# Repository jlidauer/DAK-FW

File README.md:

# DAK
### Double Action Keyboard Firmware
This firmware is used for Double Action Keyboards with Teensy microcontrollers. Currently the firmware provides two independed layers _(normal-layer and FN-layer)_, both of these layers support double action _(first action, second action)_. This means that each double action key can be configured to have up to four independent actions. The firmware is developed using the Arduino IDE with the Teensyduino add-on.

### Double Action Keyboard PCB V1.0
An example implementation a double action keyboard PCB can be found in the PCB directory.

### What is a Double Action Keyboard?
A double action keyboard has switches that have two physical positions (two steps). Each key has two different functions that can be triggered without pressing modifier keys, this makes typing of special characters easier. For example, when pressing a key one step down, the keyboard could send a normal key stroke (e.g., `KEY_A`), and if the same key would be pressed two steps down instead, the keyboard could send the key combination of a special character (e.g., `ALTGR + KEY_9`). 

More info can be found in the Wiki: [Building a Double Action Keyboard](https://github.com/jlidauer/DAK/wiki/Building-a-Double-Action-Keyboard).

### Compatible microcontrollers:
In principle all Teensy microcontrollers with keyboard funtionality should work.

The firmware has been tested with the following microcontrollers:
- Teensy 3.2
- Teensy-LC

### How to use this firmware?
See the Wiki for instructions: [Getting Started](https://github.com/jlidauer/DAK/wiki/Getting-Started)

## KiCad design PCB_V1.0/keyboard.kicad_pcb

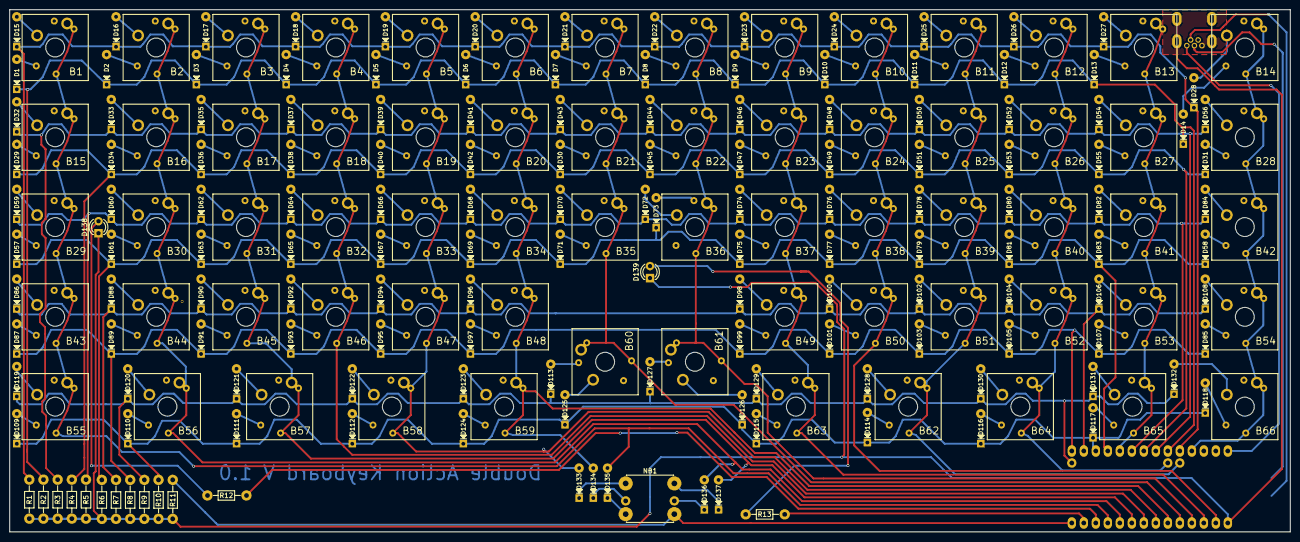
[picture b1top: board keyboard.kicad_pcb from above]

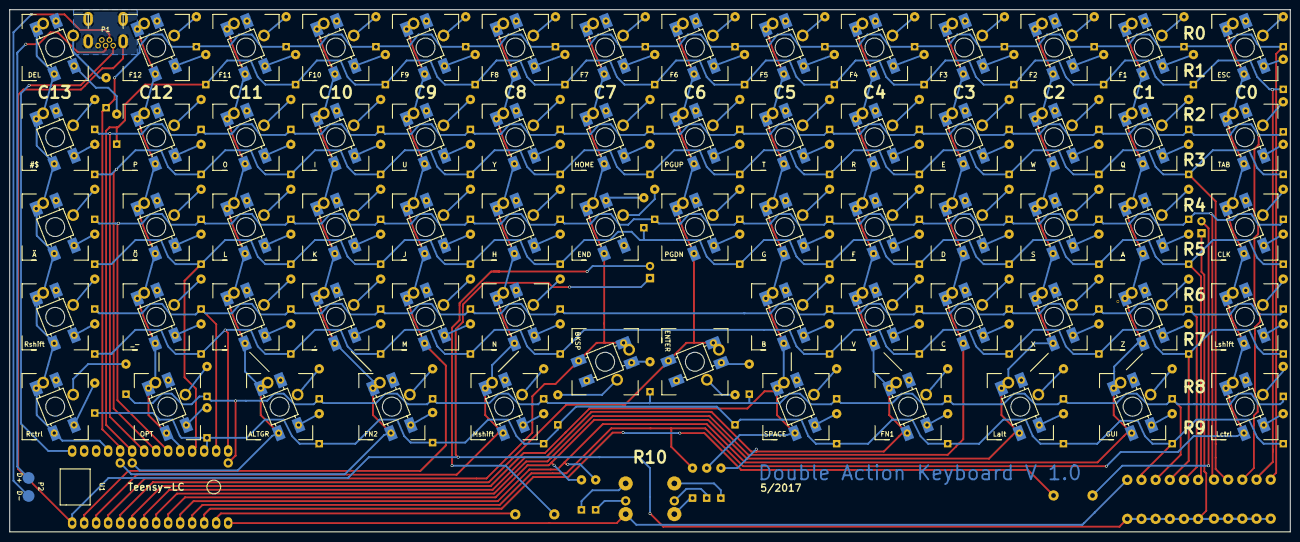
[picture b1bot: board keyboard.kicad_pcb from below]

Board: 2 copper layers, 271.0 x 110.5 mm, 222 parts (2 on the bottom side), 170 nets.

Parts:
B1: ESC; Double_Action_Switch
B2: F1; Double_Action_Switch
B3: F2; Double_Action_Switch
B4: F3; Double_Action_Switch
B5: F4; Double_Action_Switch
B6: F5; Double_Action_Switch
B7: F6; Double_Action_Switch
B8: F7; Double_Action_Switch
B9: F8; Double_Action_Switch
B10: F9; Double_Action_Switch
B11: F10; Double_Action_Switch
B12: F11; Double_Action_Switch
B13: F12; Double_Action_Switch
B14: DEL; Double_Action_Switch
B15: TAB; Double_Action_Switch
B16: Q; Double_Action_Switch
B17: W; Double_Action_Switch
B18: E; Double_Action_Switch
B19: R; Double_Action_Switch
B20: T; Double_Action_Switch
B21: PGUP; Double_Action_Switch
B22: HOME; Double_Action_Switch
B23: Y; Double_Action_Switch
B24: U; Double_Action_Switch
B25: I; Double_Action_Switch
B26: O; Double_Action_Switch
B27: P; Double_Action_Switch
B28: #$; Double_Action_Switch
B29: CLK; Double_Action_Switch
B30: A; Double_Action_Switch
B31: S; Double_Action_Switch
B32: D; Double_Action_Switch
B33: F; Double_Action_Switch
B34: G; Double_Action_Switch
B35: PGDN; Double_Action_Switch
B36: END; Double_Action_Switch
B37: H; Double_Action_Switch
B38: J; Double_Action_Switch
B39: K; Double_Action_Switch
B40: L; Double_Action_Switch
B41: Ö; Double_Action_Switch
B42: Ä; Double_Action_Switch
B43: Lshift; Double_Action_Switch
B44: Z; Double_Action_Switch
B45: X; Double_Action_Switch
B46: C; Double_Action_Switch
B47: V; Double_Action_Switch
B48: B; Double_Action_Switch
B49: N; Double_Action_Switch
B50: M; Double_Action_Switch
B51: ,; Double_Action_Switch
B52: .; Double_Action_Switch
B53: _-; Double_Action_Switch
B54: Rshift; Double_Action_Switch
B55: Lctrl; Double_Action_Switch
B56: GUI; Double_Action_Switch
B57: Lalt; Double_Action_Switch
B58: FN1; Double_Action_Switch
B59: SPACE; Double_Action_Switch
B60: ENTER; Double_Action_Switch
B61: BKSP; Double_Action_Switch
B62: FN2; Double_Action_Switch
B63: Mshift; Double_Action_Switch
B64: ALTGR; Double_Action_Switch
B65: OPT; Double_Action_Switch
B66: Rctrl; Double_Action_Switch
D1, D2, D3, D4, D5, D6, D7, D8, D9, D10, D12, D13, D14, D15, D16, D17, D18, D19, D20, D21, D22, D23, D24, D25, D26, D27, D28, D29, D30, D31, D32, D33, D34, D35, D36, D37, D38, D39, D40, D41, D42, D43, D44, D45, D46, D47, D48, D49, D50, D51, D52, D53, D54, D55, D56, D57, D58, D59, D60, D61, D62, D63, D64, D65, D66, D67, D68, D69, D70, D71, D72, D73, D74, D75, D76, D77, D78, D79, D80, D81, D82, D83, D84, D85, D86, D87, D88, D89, D90, D91, D92, D93, D94, D95, D96, D97, D98, D99, D100, D101, D102, D103, D104, D105, D106, D107, D108, D109, D110, D111, D112, D113, D114, D115, D116, D117, D118, D119, D120, D121, D122, D123, D124, D125, D126, D127, D128, D129, D130, D131, D132, D133, D134, D135, D136, D137: 1N4148; diodeDO35
D11: D_Small; diodeDO35
D138: LED_left; LED_D3.0mm
D139: LED_right; LED_D3.0mm
NB1: SKQUCAA010_ALPS
P1: USB_mini; USB_mini_B
P2: USB_PADS; SMD_pad_2x
R1, R2, R3, R4, R5, R6, R7, R8, R9, R10, R11: 5k; resistor
R12, R13: 324; resistor
U1: Teensy-LC; Teensy_LC

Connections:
C0: B1.2, B15.2, B29.2, B43.2, B55.2, D135.2, U1.9
C1: B2.2, B16.2, B30.2, B44.2, B56.2, D136.2, U1.8
C2: B3.2, B17.2, B31.2, B45.2, B57.2, D137.2, U1.7
C3: B4.2, B18.2, B32.2, B46.2, U1.6
C4: B5.2, B19.2, B33.2, B47.2, B58.2, D133.2, U1.5
C5: B6.2, B20.2, B34.2, B48.2, B59.2, D134.2, U1.4
C6: B7.2, B21.2, B35.2, B60.2, U1.3
C7: B8.2, B22.2, B36.2, B61.2, U1.2
C8: B9.2, B23.2, B37.2, B49.2, B63.2, U1.1
C9: B10.2, B24.2, B38.2, B50.2, U1.0
C10: B11.2, B25.2, B39.2, B51.2, B62.2, U1.32
C11: B12.2, B26.2, B40.2, B52.2, B64.2, U1.33
C12: B13.2, B27.2, B41.2, B53.2, B65.2, U1.22
C13: B14.2, B28.2, B42.2, B54.2, B66.2, U1.28
Earth: D138.1, D139.1, P1.5, P1.6, R1.2, R2.2, R3.2, R4.2, R5.2, R6.2, R7.2, R8.2, R9.2, R10.2, R11.2, U1.-1
unnamed: B1.1, D15.2
unnamed: B1.3, D1.2
unnamed: B2.1, D16.2
unnamed: B2.3, D2.2
unnamed: B3.1, D17.2
unnamed: B3.3, D3.2
unnamed: B4.1, D18.2
unnamed: B4.3, D4.2
unnamed: B5.1, D19.2
unnamed: B5.3, D5.2
unnamed: B6.1, D20.2
unnamed: B6.3, D6.2
unnamed: B7.1, D21.2
unnamed: B7.3, D7.2
unnamed: B8.1, D22.2
unnamed: B8.3, D8.2
unnamed: B9.1, D23.2
unnamed: B9.3, D9.2
unnamed: B10.1, D24.2
unnamed: B10.3, D10.2
unnamed: B11.1, D25.2
unnamed: B11.3, D11.2
unnamed: B12.1, D26.2
unnamed: B12.3, D12.2
unnamed: B13.1, D27.2
unnamed: B13.3, D13.2
unnamed: B14.1, D28.2
unnamed: B14.3, D14.2
unnamed: B15.1, D32.2
unnamed: B15.3, D29.2
unnamed: B16.1, D33.2
unnamed: B16.3, D34.2
unnamed: B17.1, D35.2
unnamed: B17.3, D36.2
unnamed: B18.1, D37.2
unnamed: B18.3, D38.2
unnamed: B19.1, D39.2
unnamed: B19.3, D40.2
unnamed: B20.1, D41.2
unnamed: B20.3, D42.2
unnamed: B21.1, D43.2
unnamed: B21.3, D30.2
unnamed: B22.1, D44.2
unnamed: B22.3, D45.2
unnamed: B23.1, D46.2
unnamed: B23.3, D47.2
unnamed: B24.1, D48.2
unnamed: B24.3, D49.2
unnamed: B25.1, D50.2
unnamed: B25.3, D51.2
unnamed: B26.1, D52.2
unnamed: B26.3, D53.2
unnamed: B27.1, D54.2
unnamed: B27.3, D55.2
unnamed: B28.1, D56.2
unnamed: B28.3, D31.2
unnamed: B29.1, D59.2
unnamed: B29.3, D57.2
unnamed: B30.1, D60.2
unnamed: B30.3, D61.2
unnamed: B31.1, D62.2
unnamed: B31.3, D63.2
unnamed: B32.1, D64.2
unnamed: B32.3, D65.2
unnamed: B33.1, D66.2
unnamed: B33.3, D67.2
unnamed: B34.1, D68.2
unnamed: B34.3, D69.2
unnamed: B35.1, D70.2
unnamed: B35.3, D71.2
unnamed: B36.1, D72.2
unnamed: B36.3, D73.2
unnamed: B37.1, D74.2
unnamed: B37.3, D75.2
unnamed: B38.1, D76.2
unnamed: B38.3, D77.2
unnamed: B39.1, D78.2
unnamed: B39.3, D79.2
unnamed: B40.1, D80.2
unnamed: B40.3, D81.2
unnamed: B41.1, D82.2
unnamed: B41.3, D83.2
unnamed: B42.1, D84.2
unnamed: B42.3, D58.2
unnamed: B43.1, D86.2
unnamed: B43.3, D87.2
unnamed: B44.1, D88.2
unnamed: B44.3, D89.2
unnamed: B45.1, D90.2
unnamed: B45.3, D91.2
unnamed: B46.1, D92.2
unnamed: B46.3, D93.2
unnamed: B47.1, D94.2
unnamed: B47.3, D95.2
unnamed: B48.1, D96.2
unnamed: B48.3, D97.2
unnamed: B49.1, D98.2
unnamed: B49.3, D99.2
unnamed: B50.1, D100.2
unnamed: B50.3, D101.2
unnamed: B51.1, D102.2
unnamed: B51.3, D103.2
unnamed: B52.1, D104.2
unnamed: B52.3, D105.2
unnamed: B53.1, D106.2
unnamed: B53.3, D107.2
unnamed: B54.1, D108.2
unnamed: B54.3, D85.2
unnamed: B55.1, D119.2
unnamed: B55.3, D109.2
unnamed: B56.1, D120.2
unnamed: B56.3, D110.2
unnamed: B57.1, D121.2
unnamed: B57.3, D111.2
unnamed: B58.1, D122.2
unnamed: B58.3, D112.2
unnamed: B59.1, D123.2
unnamed: B59.3, D124.2
unnamed: B60.1, D125.2
unnamed: B60.3, D113.2
unnamed: B61.1, D126.2
unnamed: B61.3, D127.2
unnamed: B62.1, D128.2
unnamed: B62.3, D114.2
unnamed: B63.1, D129.2
unnamed: B63.3, D115.2
unnamed: B64.1, D130.2
unnamed: B64.3, D116.2
unnamed: B65.1, D131.2
unnamed: B65.3, D117.2
unnamed: B66.1, D132.2
unnamed: B66.3, D118.2
unnamed: D133.1, NB1.1
unnamed: D134.1, NB1.2
unnamed: D135.1, NB1.3
unnamed: D136.1, NB1.5
unnamed: D137.1, NB1.6
unnamed: D138.2, R12.2
unnamed: D139.2, R13.2
unnamed: P1.2, P2.2
unnamed: P1.3, P2.1
unnamed: R12.1, U1.10
unnamed: R13.1, U1.11
R0: D15.1, D16.1, D17.1, D18.1, D19.1, D20.1, D21.1, D22.1, D23.1, D24.1, D25.1, D26.1, D27.1, D28.1, R1.1, U1.27
R1: D1.1, D2.1, D3.1, D4.1, D5.1, D6.1, D7.1, D8.1, D9.1, D10.1, D11.1, D12.1, D13.1, D14.1, R2.1, U1.26
R2: D32.1, D33.1, D35.1, D37.1, D39.1, D41.1, D43.1, D44.1, D46.1, D48.1, D50.1, D52.1, D54.1, D56.1, R3.1, U1.25
R3: D29.1, D30.1, D31.1, D34.1, D36.1, D38.1, D40.1, D42.1, D45.1, D47.1, D49.1, D51.1, D53.1, D55.1, R4.1, U1.24
R4: D59.1, D60.1, D62.1, D64.1, D66.1, D68.1, D70.1, D72.1, D74.1, D76.1, D78.1, D80.1, D82.1, D84.1, R5.1, U1.23
R5: D57.1, D58.1, D61.1, D63.1, D65.1, D67.1, D69.1, D71.1, D73.1, D75.1, D77.1, D79.1, D81.1, D83.1, R6.1, U1.21
R6: D86.1, D88.1, D90.1, D92.1, D94.1, D96.1, D98.1, D100.1, D102.1, D104.1, D106.1, D108.1, R7.1, U1.19
R7: D85.1, D87.1, D89.1, D91.1, D93.1, D95.1, D97.1, D99.1, D101.1, D103.1, D105.1, D107.1, R8.1, U1.18
R8: D113.1, D119.1, D120.1, D121.1, D122.1, D123.1, D127.1, D128.1, D129.1, D130.1, D131.1, D132.1, R9.1, U1.17
R9: D109.1, D110.1, D111.1, D112.1, D114.1, D115.1, D116.1, D117.1, D118.1, D124.1, D125.1, D126.1, R10.1, U1.20
R10: NB1.4, R11.1, U1.12
VCC: P1.1, U1.31

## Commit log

2017-03-04 photos
2017-03-04 source
2017-08-02 bug fixed
2018-02-19 Bug fix, unwanted keystrokes eliminated when FN-layer is released
2018-03-08 PCB files added.
2022-11-20 new FW version 1.1, with two double action layers
2022-11-20 rename pcb
2022-11-20 comment
